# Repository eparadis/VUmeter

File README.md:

### VU meter driving circuit

This circuit is designed to drive a ~500uA meter.

It is inspired by and largely based off [the ideas here](http://objectivesounds.co.uk/articles/vu-meter/).

It is setup for a single-sided supply of my own devising, as when I had originally written this up in my notebook, I did not include the original author's single-sided design. Since I was using a single meter but a dual opamp, I had an extra opamp to create a reference voltage. The original author envisioned using each of the opamps as half a stereo pair.

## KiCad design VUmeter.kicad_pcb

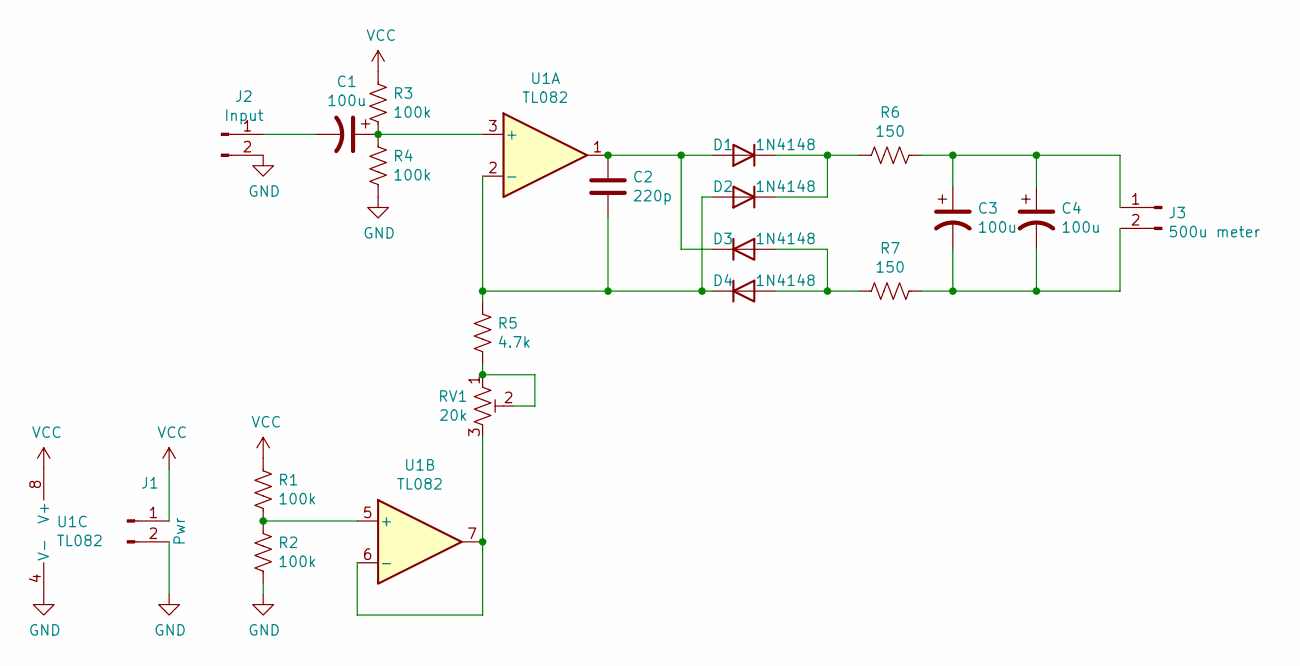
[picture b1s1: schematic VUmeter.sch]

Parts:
C1, C3, C4: 100u; CP_Radial_D8.0mm_P2.50mm
C2: 220p; C_Disc_D5.0mm_W2.5mm_P5.00mm
D1, D2, D3, D4: 1N4148; D_DO-35_SOD27_P7.62mm_Horizontal
J1: Pwr; PinHeader_1x02_P2.54mm_Vertical
J2: Input; PinHeader_1x02_P2.54mm_Vertical
J3: 500u meter; PinHeader_1x02_P2.54mm_Vertical
R1, R2, R3, R4: 100k; R_Axial_DIN0207_L6.3mm_D2.5mm_P7.62mm_Horizontal
R5: 4.7k; R_Axial_DIN0207_L6.3mm_D2.5mm_P7.62mm_Horizontal
R6, R7: 150; R_Axial_DIN0207_L6.3mm_D2.5mm_P7.62mm_Horizontal
RV1: 20k; Potentiometer_Alpha_RD901F-40-00D_Single_Vertical_CircularH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
U1: TL082; DIP-8_W7.62mm_LongPads

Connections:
GND: J1.2, J2.2, R2.2, R4.2, U1.4 (V-)
unnamed: C1.1, R3.2, R4.1, U1.3 (+)
unnamed: C1.2, J2.1
unnamed: C2.1, D1.2 (A), D3.1 (K), U1.1
unnamed: C2.2, D2.2 (A), D4.1 (K), R5.1, U1.2 (-)
unnamed: C3.1, C4.1, J3.1, R6.1
unnamed: C3.2, C4.2, J3.2, R7.1
unnamed: D1.1 (K), D2.1 (K), R6.2
unnamed: D3.2 (A), D4.2 (A), R7.2
unnamed: R1.2, R2.1, U1.5 (+)
unnamed: R5.2, RV1.1, RV1.2
unnamed: RV1.3, U1.6 (-), U1.7
VCC: J1.1, R1.1, R3.1, U1.8 (V+)

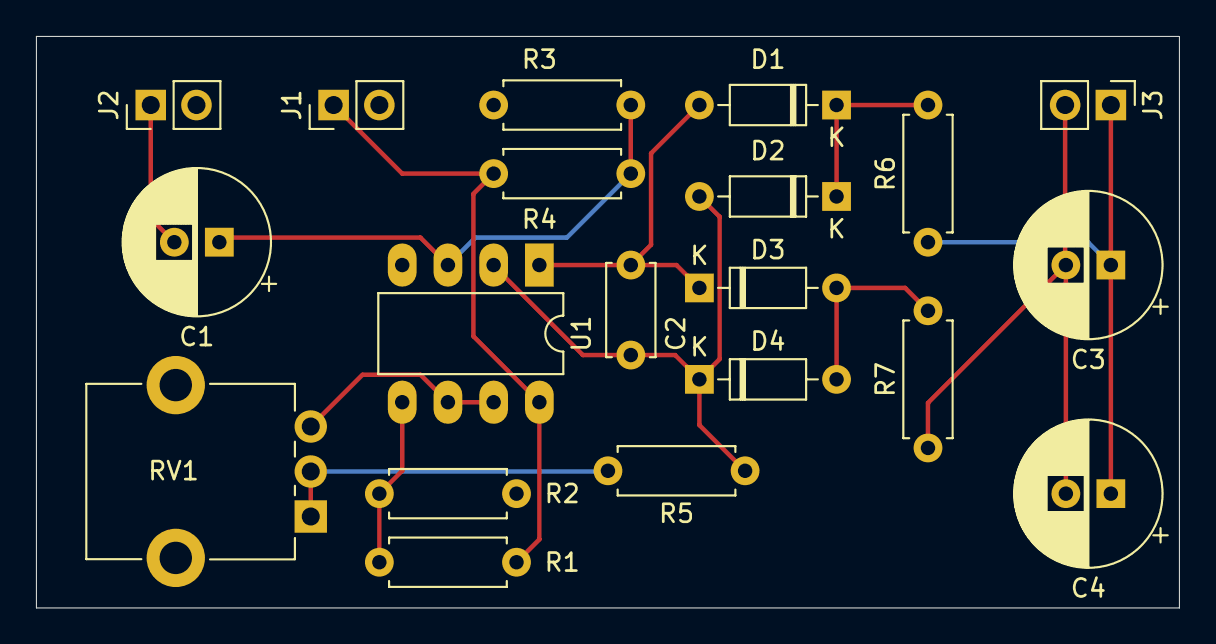
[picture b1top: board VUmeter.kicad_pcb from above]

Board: 2 copper layers, 63.5 x 31.8 mm, 20 parts (0 on the bottom side), 13 nets.

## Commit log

2021-08-02 standard kicad gitignore
2021-08-02 first pass on schematic and pcb
2021-08-02 thoughts on origin
